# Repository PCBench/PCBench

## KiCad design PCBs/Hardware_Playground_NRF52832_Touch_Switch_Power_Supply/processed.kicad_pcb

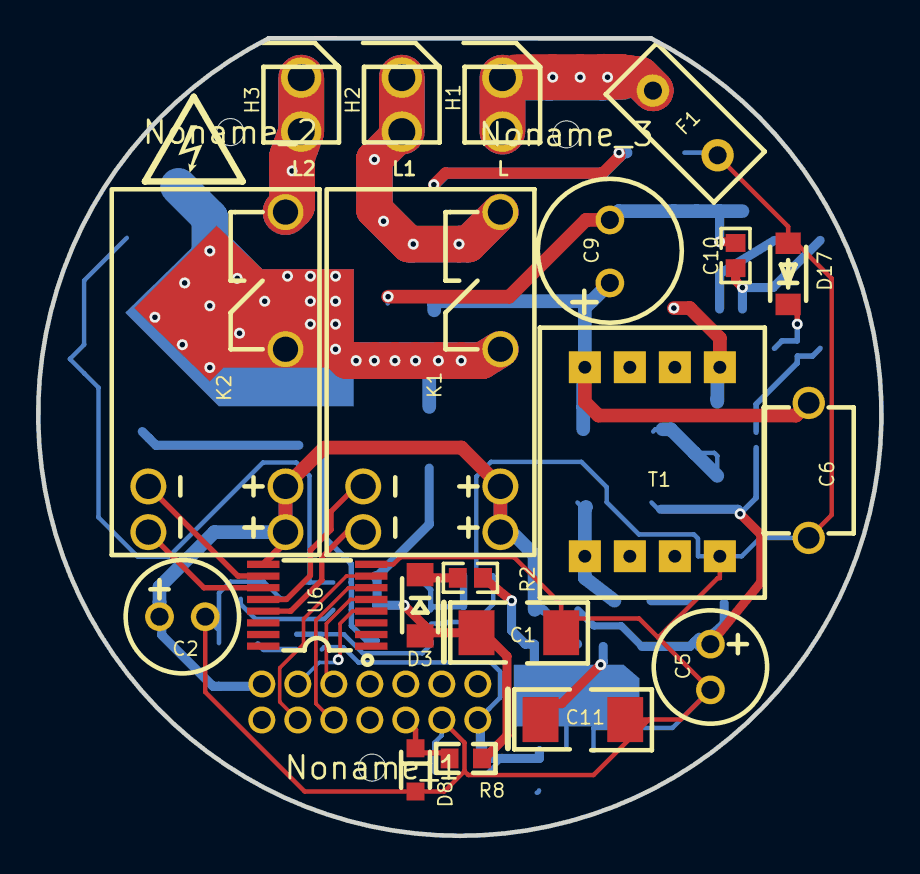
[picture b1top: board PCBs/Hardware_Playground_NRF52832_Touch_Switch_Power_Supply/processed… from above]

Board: 2 copper layers, 46.8 x 44.3 mm, 56 parts (0 on the bottom side), 37 nets.

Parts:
C1, C11: 22uF; CAP-SMD_L6.0-W3.2
C2, C5: 330uF; CAP-TH_BD6.3-P2.50-D1.0-FD
C3: CAP-SMD_L3.5-W2.8-R-RD
C4: 680nF; 0805
C6: 1nF; CAP-TH_L7.0-W5.0-P7.50-D1.2
C7: 27pF; 0805
C9: 4.7uF; CAP-TH_BD8.0-P3.50-D1.0-FD
C10: 100nF; 0603
CN1: 2X7P; A2005WV-2X7P
D1: B340LB-13-F; SMB_L4.6-W3.6-LS5.3-RD
D2, D3: 1N4007W; SOD-123FL_L2.7-W1.8-LS3.8-RD
D4, D7, D12: BAV21WS; SOD-323_L1.8-W1.3-LS2.5-RD
D5, D6: MMSZ5242BS; SOD-323_L1.8-W1.3-LS2.5-RD
D8: BZT52C3V3S; SOD-323_L1.8-W1.3-LS2.5-RD
D13: MB6S; MBS
D14: SS14; SMA_L4.3-W2.6-LS5.2-FD
D15: SMBJ130A; SMB_L4.6-W3.6-LS5.3-RD
D16: US1M; SMA(DO-214AC)
D17: MMSZ5242; SOD-123_L2.8-W1.8-LS3.7-RD
F1: SMT1500A; FUSE-TH_L8.5-W4.0-P5.08-D0.6
H1: L; 360273
H2: L1; 360273
H3: L2; 360273
HV2: IEC_HighVoltage; IEC_HIGHVOLTAGE_SMALL
K1, K2: HFE60-12-1HT-L2; RELAY-TH_HFE60-12-1HST-L2
LG: my_logo; gge1185
Noname_1, Noname_2, Noname_3: MountingHole_1.50mm
Q1: IRLR8726PBF; TO-252-2_L6.6-W6.1-P4.57-LS9.9-BR-CW
Q2: MMBT3904; SOT-23(SOT-23-3)
R1, R2: 47; 0603
R3: 20K; 0402
R4: 10K; 0402
R5, R6: 100K; R0402
R7: 33K; 0402
R8: 1K; R0603
R16: 390; 0805
R18: 22; 0402
R19: 1K; 0402
R20: 10; 1206
T1: EE10A-1
U1: LM321; SOT-23-5_L3.0-W1.7-P0.95-LS2.8-BL
U2: MCP1703T-3302; SOT-89-3_L4.5-W2.5-P1.50-LS4.2-BR
U3: EL357; SOP-4_P2.54
U4: LNK364DN-TL; SO-8_7P-L4.9-W3.9-P1.27-LS5.9-BL-PE3
U6: TPL7407LPWR; TSSOP-16_L5.0-W4.4-P0.65-LS6.4-BL

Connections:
+3V3: C3.1, CN1.2, R4.2, U2.3
+12V: C2.1, CN1.13, D4.1, D5.1, D7.1, K1.1, K1.2, K2.1, K2.2, U6.9
AC_DC_N: D13.1, H2.1, H2.2, K1.8
C9_1: C6.2, C9.1, D13.3, D15.2, T1.1
CH1_RST: CN1.9, U6.5
CH1_SET: CN1.11, U6.4
CH2_RST: CN1.12, U6.7
CH2_SET: CN1.10, U6.6
D1_1: D1.1, D2.2, K1.5, K2.5, Q1.2
D12_2: C5.1, C7.2, D7.2, D12.2, D14.2, R18.2
D13_2: D13.2, R20.2
D16_2: D15.1, D16.2
F1_2: F1.2, H1.1, H1.2
GND: C1.2, C2.2, C3.2, C4.1, C5.2, C6.1, C11.2, CN1.4, D1.2, D5.2, D8.2, D17.2, F1.1, Q1.3, Q2.2, R6.1, R7.1, R20.1, T1.5, U1.2, U2.1, U6.8
H3_1: H3.1, H3.2, K2.8
K1_15: K1.15, U6.12
K1_16: K1.16, U6.13
K2_15: K2.15, U6.10
K2_16: K2.16, U6.11
Q1_1: Q1.1, R1.2
Q2_1: Q2.1, R5.1
Q2_3: Q2.3, R3.1
R2_1: D3.1, R2.1
R2_2: C11.1, D4.2, D12.1, R2.2, U2.2
R16_2: C7.1, R16.2
T1_8: D14.1, R16.1, T1.8
U1_1: C4.2, D6.2, R7.2, U1.1
U1_3: R3.2, R4.1, U1.3
U1_4: R1.1, R5.2, R6.2, U1.4
U1_5: C1.1, D2.1, D3.2, D6.1, R8.2, U1.5
U3_1: R18.1, R19.2, U3.1
U3_2: D17.1, R19.1, U3.2
U3_3: U3.3, U4.2
U3_4: C10.1, U3.4, U4.1
U4_4: D16.1, T1.4, U4.4
U4_5: C9.2, C10.2, D13.4, U4.5, U4.6, U4.7, U4.8
VSENSE: CN1.6, D8.1, R8.1

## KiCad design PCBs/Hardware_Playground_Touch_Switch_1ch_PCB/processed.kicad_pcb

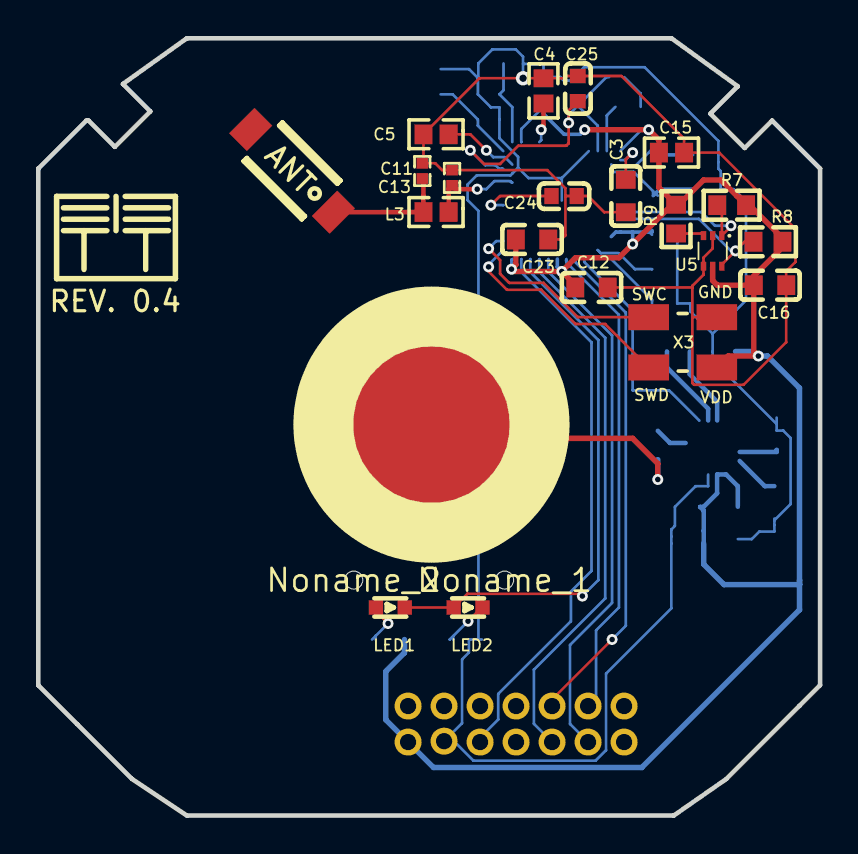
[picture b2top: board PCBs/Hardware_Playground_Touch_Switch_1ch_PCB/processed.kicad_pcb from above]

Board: 2 copper layers, 43.4 x 43.2 mm, 49 parts (0 on the bottom side), 37 nets.

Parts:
ALG: my_logo; ggeac4e8891367b2b2c
C1, C15, C17: 1uF; 0603
C2, C3, C12, C16, C18, C19, C20, C23: 100nF; C0603
C4: N.C.; 0603
C5: 100pF; 0603
C6: 2.2nF; C0603
C7, C8, C9, C10: 22pF; 0603
C11, C13: 0.5pF; 0402
C14, C21, C22: 4.7uF; 0603
C24: 820pF; C0603
C25: 47nF; C0603
CN1: 2X7P; HDR-TH_14P-P2.00-V-R2-C7-S2.00_A2005HWV-2X7P
H1: PROG; CONNECTER_SMD_1.27_1X4_D180
L2: 10uH; 0603
L3: 3.3nH; 0603
L4: 15nH; 0402
LED1: RED; LED-SMD_0603-T
LED2: BLUE; LED-SMD_0603-T
Noname_1, Noname_2: MountingHole_1.00mm
R5, R6, R7, R8, R9: 4.7K; R0603
R10: 560; R0603
U1: NRF52840-QIAA-R; AQFN-73_L7.0-W7.0-P0.50-BL-EP4.8
U3: Antenna 2.4GHz; AN6520
U5: TMP112; SOT-563_L1.6-W1.2-P0.50-LS1.6-BL
U6: CY8C4014LQI-421T; QFN-16_L3.0-W3.0-P0.50-BL-EP1.7
U7: TS1; LIVOLO_TOUCH_PAD
X1: 32MHz; OSC-SMD_4P-L2.0-W1.6-BL
X2: 32.768KHz; FC-135R_L3.2-W1.5
X3: ICSP; SWD4_5032

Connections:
ANT: C11.1, L3.1, U1.H23
C4_2: C4.2, U1.A18
CH1_LED: LED1.1, LED2.2, U1.AD20
DCC: L2.1, U1.B3
DEC4_6: C1.1, C25.2, L4.2, U1.B5, U1.E24
GND: C1.2, C2.1, C3.2, C4.1, C5.2, C6.2, C7.2, C8.2, C9.1, C10.1, C11.2, C12.1, C13.2, C14.1, C15.1, C16.2, C17.1, C18.1, C19.1, C20.1, C21.1, C22.1, C23.1, C24.1, C25.1, CN1.11, H1.3, R5.2, U1.0, U1.B7, U1.F23, U5.2, U5.4, U6.7, X1.2, X1.4, X3.3
L2_2: L2.2, L4.1
L3_2: C13.1, L3.2, U3.1
LED2_1: LED2.1, R5.1
MTO: U1.AD8, U6.13
R1_RST: CN1.6, U1.AD10
R1_SET: CN1.4, U1.AD12
R2_RST: CN1.3, U1.AD16
R2_SET: CN1.5, U1.AD18
R6_1: LED1.2, R6.1
R9_1: R9.1, U5.3
R10_1: R10.1, U7.1
SCL: R7.2, U1.N1, U5.1
SDA: R8.2, U1.R1, U5.6
SWC: H1.2, U6.15
SWCLK: U1.AA24, X3.4
SWD: H1.1, U6.14
SWDIO: U1.AC24, X3.1
U1_AC5: C21.2, U1.AC5
U1_AD2: C22.2, U1.AD2
U1_C1: C3.1, U1.C1
U1_D23: C5.1, U1.D23
U1_N24: C24.2, U1.N24
U6_3: C6.1, U6.3
U6_4: C19.2, U6.4
U6_11: R10.2, U6.11
VDD: C2.2, C12.2, C14.2, C15.2, C16.1, C17.2, C18.2, C20.2, C23.2, CN1.13, H1.4, R6.2, R7.1, R8.1, R9.2, U1.A22, U1.AD14, U1.AD23, U1.B1, U1.W1, U1.Y2, U5.5, U6.5, U6.6, X3.2
VSENSE: CN1.9, U1.AD22
XC1: C7.1, U1.B24, X1.1
XC2: C8.1, U1.A23, X1.3
XL1: C9.2, U1.D2, X2.1
XL2: C10.2, U1.F2, X2.2

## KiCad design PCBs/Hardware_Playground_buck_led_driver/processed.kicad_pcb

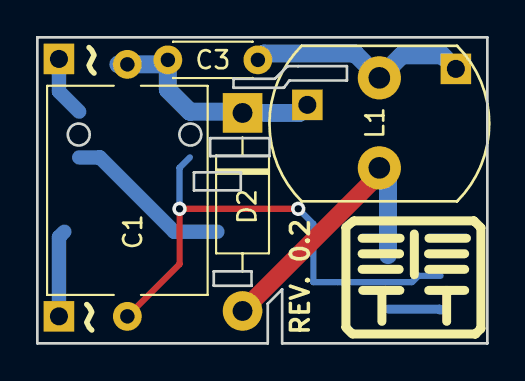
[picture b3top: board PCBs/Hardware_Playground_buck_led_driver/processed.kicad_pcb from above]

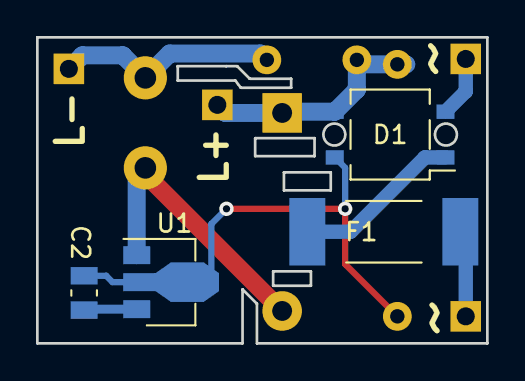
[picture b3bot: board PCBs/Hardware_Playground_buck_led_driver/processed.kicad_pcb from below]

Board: 2 copper layers, 25.0 x 17.0 mm, 12 parts (4 on the bottom side), 8 nets.

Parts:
C1: 100n/400Vdc; C_Rect_L11.5mm_W8.8mm_P10.00mm_MKT
C2: 0.1u; C_0805_2012Metric
C3: 10n/100Vdc; C_Disc_D4.3mm_W1.9mm_P5.00mm
D1: MB10S; TO-269AA
D2: MUR160; D_DO-41_SOD81_P10.16mm_Horizontal
F1: 0.5A; R_2512_6332Metric
J1, J2: AC_IN; PinHeader_1x01_P2.54mm_Vertical
J3: LED+; PinHeader_1x01_P2.54mm_Vertical
J4: LED-; PinHeader_1x01_P2.54mm_Vertical
L1: 39mH; L_Radial_D12.0mm_P5.00mm_Neosid_SD12k_style2
U1: HV9922N8-G; SOT-89-3

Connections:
GND: C1.2, C2.1, D1.4, U1.2
unnamed: C1.1, C3.1, D1.3, D2.1, J3.1
unnamed: C2.2, U1.3
unnamed: C3.2, J4.1, L1.1
unnamed: D1.1, F1.1
unnamed: D1.2, J1.1
unnamed: D2.2, L1.2, U1.1
unnamed: F1.2, J2.1

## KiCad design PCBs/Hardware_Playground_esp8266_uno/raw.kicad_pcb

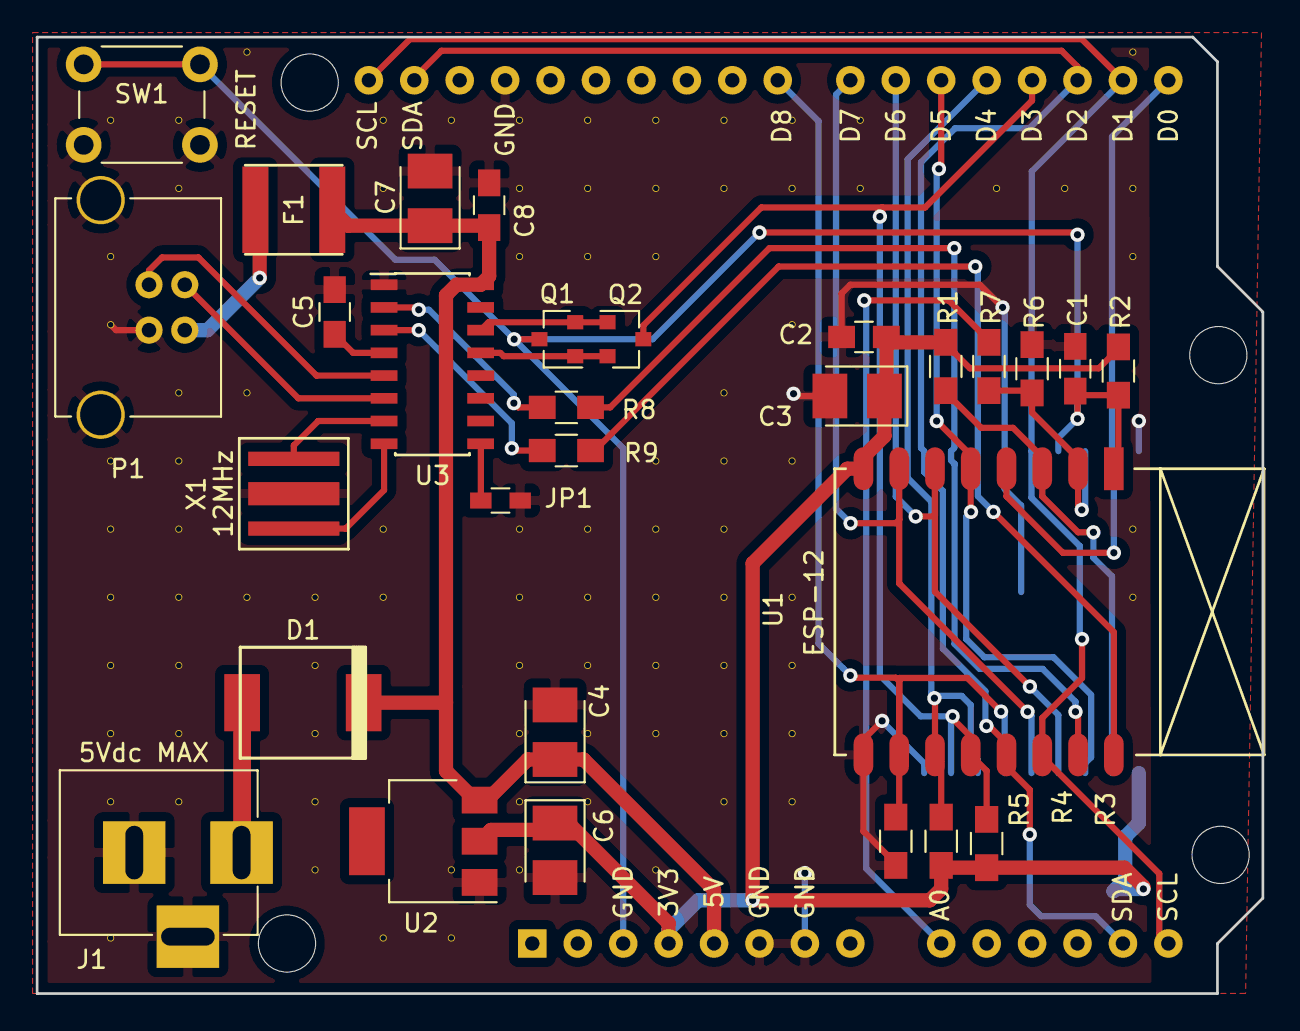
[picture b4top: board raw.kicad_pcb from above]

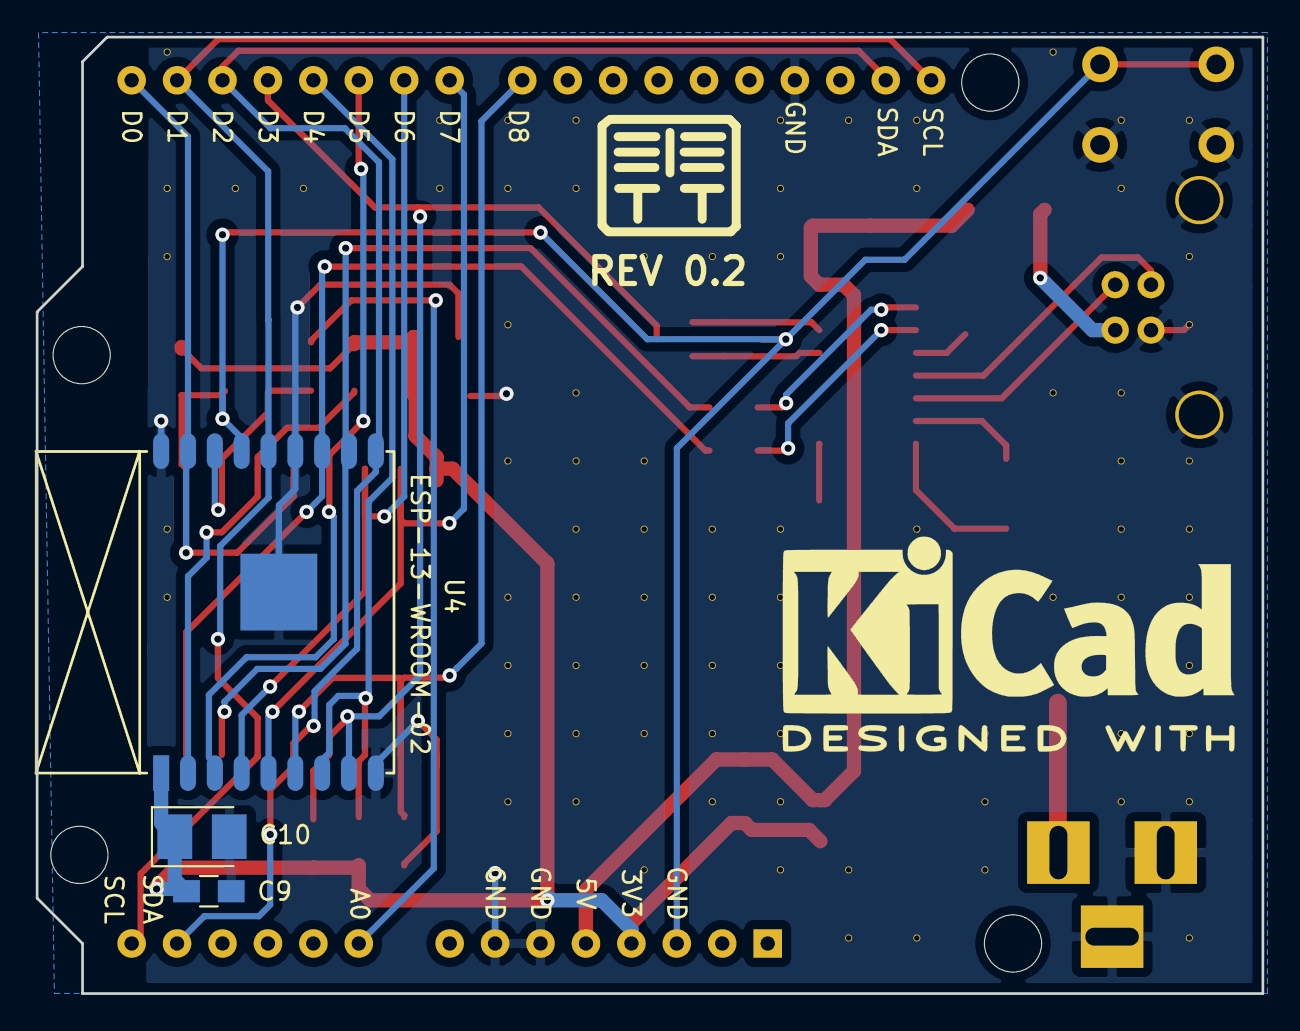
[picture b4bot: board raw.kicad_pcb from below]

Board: 2 copper layers, 68.5 x 53.5 mm, 120 parts (4 on the bottom side), 30 nets.

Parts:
A1: Arduino_UNO_R3
C1, C2, C8, C9: 100n; C_0805_HandSoldering
C3, C7, C10: 10u; CP_Tantalum_Case-B_EIA-3528-21_Reflow
C4, C6: 22u; CP_Tantalum_Case-B_EIA-3528-21_Reflow
C5: 10n; C_0805_HandSoldering
D1: SS34; do214ab
F1: MF-SMDF050; mf-smdf050
J1: Barrel_Jack; BARREL_JACK
JP1: CTS; R_0603_HandSoldering
P1: USB; USB_B
Q1, Q2: 2N2222; SOT-23
R1, R2, R3, R4, R5: 10K; R_0805_HandSoldering
R6: 100K; R_0805_HandSoldering
R7: 220K; R_0805_HandSoldering
R8, R9: 470; R_0805_HandSoldering
SW1: RESET; SW_PUSH_6mm
U1: ESP-12
U2: AMS1117-3.3; SOT-223
U3: CH340G; SOIC-16_3.9x9.9mm_Pitch1.27mm
U4: ESP-13-WROOM-02
V3_2, V3_4, V3_5, V3_7, V3_8, V3_9, V3_10, V3_11, V3_12, V3_14, V4_2, V4_3, V4_6, V4_7, V4_8, V4_9, V4_10, V4_11, V4_12, V5_1, V5_6, V5_9, V6_9, V6_10, V6_11, V6_12, V6_13, V7_2, V7_3, V7_8, V7_9, V7_14, V8_2, V8_13, V8_14, V9_2, V9_3, V9_4, V9_8, V9_9, V9_10, V9_11, V9_12, V9_13, V10_2, V10_3, V10_4, V10_8, V10_9, V10_10, V10_11, V10_12, V11_2, V11_3, V11_4, V11_7, V11_8, V11_9, V11_10, V11_11, V11_13, V12_2, V12_3, V12_6, V12_7, V12_8, V12_9, V12_10, V12_11, V12_12, V13_2, V13_3, V13_5, V13_7, V13_9, V13_10, V13_11, V13_12, V14_2, V14_3, V16_3, V17_3, V18_1, V18_3, V18_4, V18_8, V18_9: AUTO_VIA; VIA_MATRIX
X1: 12MHz; ZTTCS-3

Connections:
+3V3: A1.4, C2.2, C3.1, C6.1, C9.2, C10.1, R1.2, R2.2, R3.2, R4.2, U1.8, U2.2, U4.1
+5V: A1.5, C4.1, C7.1, C8.2, D1.1, F1.1, U2.3, U3.16
/A0: A1.9, R7.1
/ADC: R6.1, R7.2, U1.2, U4.16
/DTR: Q1.1, Q2.2, U3.13
/EN: R1.1, U1.3, U4.2
/GPIO0: A1.18, Q2.3, R3.1, U1.12, U4.8
/GPIO2: A1.19, R4.1, U1.11, U4.7
/GPIO4: A1.13, A1.17, A1.31, U1.13, U4.10
/GPIO5: A1.14, A1.16, A1.32, U1.14, U4.14
/GPIO12: A1.21, U1.6, U4.4
/GPIO13: A1.22, U1.7, U4.5
/GPIO14: A1.20, U1.5, U4.3
/GPIO15: A1.23, R5.1, U1.10, U4.6
/GPIO16: A1.15, U1.4, U4.17
/RESET: A1.3, C1.2, Q1.3, R2.1, SW1.1, U1.1, U4.15
/RTS: Q1.2, Q2.1, U3.14
/RX: R8.2, U1.15, U4.11
/TX: R9.2, U1.16, U4.12
GND: A1.6, A1.7, A1.29, C1.1, C2.1, C3.2, C4.2, C5.2, C6.2, C7.2, C8.1, C9.1, C10.2, J1.2, J1.3, JP1.1, P1.4, P1.5, R5.2, R6.2, SW1.2, U1.9, U2.1, U3.1, U4.9, U4.13, U4.18, U4.PAD, V3_2.1, V3_4.1, V3_5.1, V3_7.1, V3_8.1, V3_9.1, V3_10.1, V3_11.1, V3_12.1, V3_14.1, V4_2.1, V4_3.1, V4_6.1, V4_7.1, V4_8.1, V4_9.1, V4_10.1, V4_11.1, V4_12.1, V5_1.1, V5_6.1, V5_9.1, V6_9.1, V6_10.1, V6_11.1, V6_12.1, V6_13.1, V7_2.1, V7_3.1, V7_8.1, V7_9.1, V7_14.1, V8_2.1, V8_13.1, V8_14.1, V9_2.1, V9_3.1, V9_4.1, V9_8.1, V9_9.1, V9_10.1, V9_11.1, V9_12.1, V9_13.1, V10_2.1, V10_3.1, V10_4.1, V10_8.1, V10_9.1, V10_10.1, V10_11.1, V10_12.1, V11_2.1, V11_3.1, V11_4.1, V11_7.1, V11_8.1, V11_9.1, V11_10.1, V11_11.1, V11_13.1, V12_2.1, V12_3.1, V12_6.1, V12_7.1, V12_8.1, V12_9.1, V12_10.1, V12_11.1, V12_12.1, V13_2.1, V13_3.1, V13_5.1, V13_7.1, V13_9.1, V13_10.1, V13_11.1, V13_12.1, V14_2.1, V14_3.1, V16_3.1, V17_3.1, V18_1.1, V18_3.1, V18_4.1, V18_8.1, V18_9.1, X1.2
unnamed: C5.1, U3.4
unnamed: D1.2, J1.1
unnamed: F1.2, P1.1
unnamed: JP1.2, U3.9
unnamed: P1.2, U3.6
unnamed: P1.3, U3.5
unnamed: R8.1, U3.2
unnamed: R9.1, U3.3
unnamed: U3.7, X1.1
unnamed: U3.8, X1.3

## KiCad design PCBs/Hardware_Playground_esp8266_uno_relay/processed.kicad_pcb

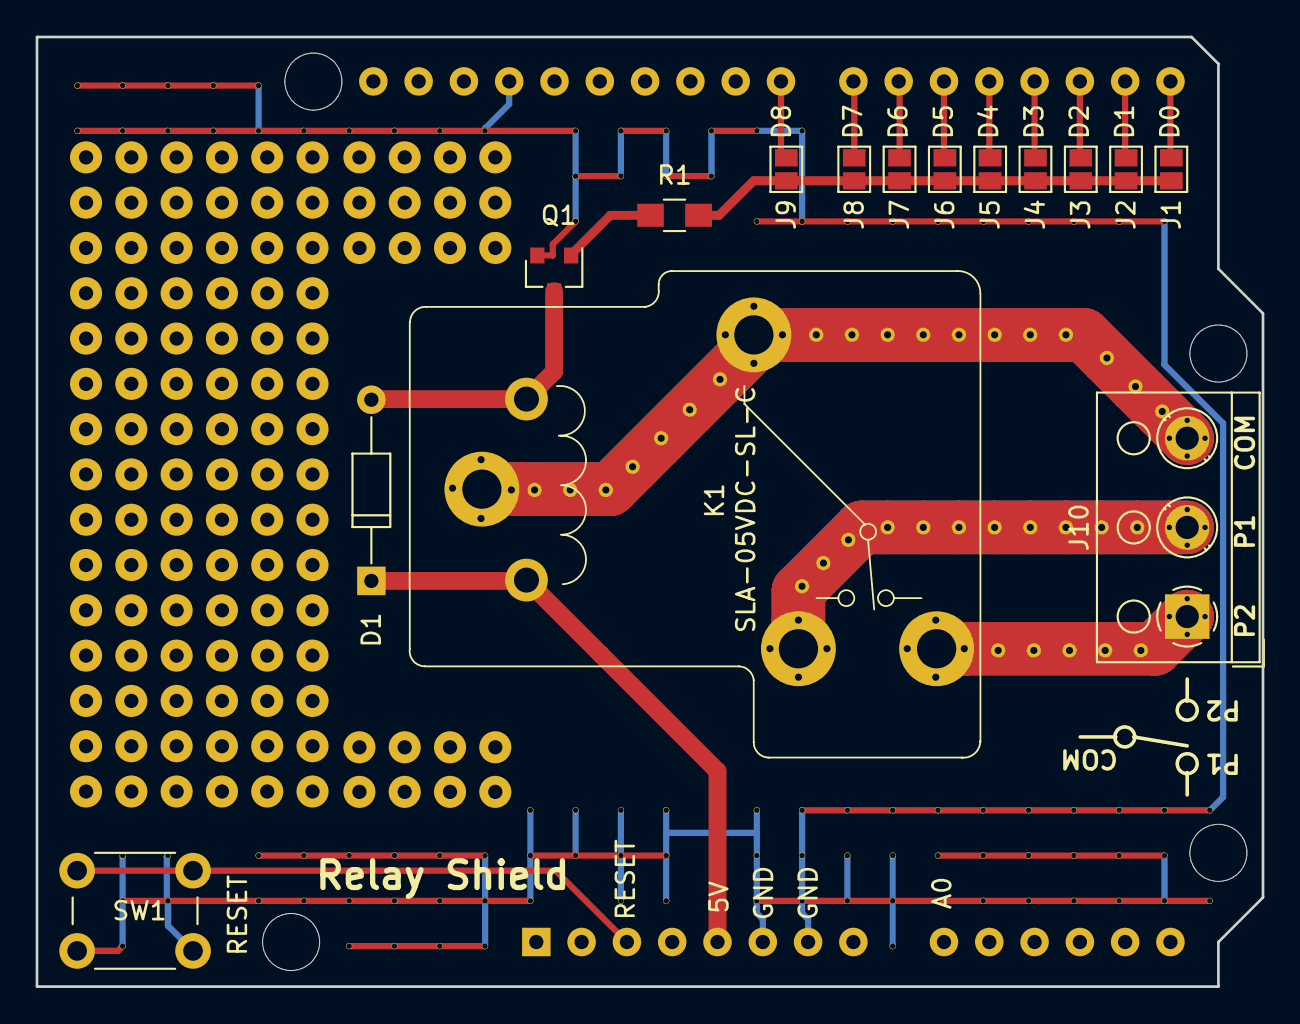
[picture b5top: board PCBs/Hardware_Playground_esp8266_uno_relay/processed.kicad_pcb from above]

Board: 2 copper layers, 68.8 x 53.2 mm, 179 parts (1 on the bottom side), 18 nets.

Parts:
A1: Arduino_UNO_R3
D1: 1N4148; D_DO-35_SOD27_P10.16mm_Horizontal
J1, J2, J3, J4, J5, J6, J7, J8, J9: GS2
J10: R_CON; TerminalBlock_RND_205-00002_Pitch5.00mm
K1: SLA-05VDC-SL-C; SLA-5VDC-SL
Q1: MMBT2222; SOT-23
R1: 1K; R_0805_HandSoldering
SW1: RESET; SW_PUSH_6mm
V5_2, V5_3, V6_2, V6_3, V6_19, V6_20, V6_21, V7_2, V7_3, V7_19, V7_20, V8_2, V8_3, V9_2, V9_3, V9_19, V9_20, V10_3, V10_19, V10_20, V11_3, V11_19, V11_20, V11_21, V12_3, V12_19, V12_20, V12_21, V13_3, V13_19, V13_20, V13_21, V14_3, V14_19, V14_20, V14_21, V15_18, V15_19, V15_20, V16_3, V16_4, V16_5, V16_18, V16_19, V17_3, V17_4, V17_18, V17_19, V17_20, V18_3, V18_4, V18_18, V18_19, V18_20, V19_3, V19_4, V20_3, V20_5, V20_18, V20_19, V20_20, V21_3, V21_5, V21_18, V21_18_2, V21_18_3, V21_18_4, V21_18_5, V21_18_6, V21_18_7, V21_18_8, V21_18_9, V21_18_10, V21_18_11, V21_18_12, V21_18_13, V21_18_14, V21_18_15, V21_18_16, V21_18_17, V21_18_18, V21_18_19, V21_18_20, V21_18_21, V21_18_22, V21_18_23, V21_18_24, V21_18_25, V21_18_26, V21_18_27, V21_18_28, V21_18_29, V21_18_30, V21_18_31, V21_18_32, V21_18_33, V21_18_34, V21_18_35, V21_18_36, V21_18_37, V21_18_38, V21_18_39, V21_18_40, V21_18_41, V21_18_42, V21_18_43, V21_18_44, V21_18_45, V21_18_46, V21_18_47, V21_18_48, V21_18_49, V21_18_50, V21_18_51, V21_18_52, V21_18_53, V21_18_54, V21_18_55, V21_18_56, V21_18_57, V21_18_58, V21_18_59, V21_18_60, V21_18_61, V21_18_62, V21_18_63, V21_19, V21_20, V22_5, V22_18, V22_19, V22_20, V23_5, V23_18, V23_19, V23_20, V23_21, V24_5, V24_18, V24_19, V24_20, V25_5, V25_18, V25_19, V25_20, V26_5, V26_18, V26_19, V26_20, V27_5, V27_18, V27_19, V27_20, V28_5, V28_18, V28_19, V28_20, V29_5, V29_18, V29_19, V29_20, V30_18, V30_20: AUTO_VIA; VIA_MATRIX

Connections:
+5V: A1.5, D1.1, K1.5
/D0: A1.15, J1.2
/D1: A1.16, J2.2
/D2: A1.17, J3.2
/D3: A1.18, J4.2
/D4: A1.19, J5.2
/D5: A1.20, J6.2
/D6: A1.21, J7.2
/D7: A1.22, J8.2
/D8: A1.23, J9.2
/REL1: J10.3, K1.1, V21_18_26.1, V21_18_27.1, V21_18_28.1, V21_18_29.1, V21_18_30.1, V21_18_31.1, V21_18_32.1, V21_18_33.1, V21_18_34.1, V21_18_35.1, V21_18_36.1, V21_18_37.1, V21_18_38.1, V21_18_39.1, V21_18_40.1, V21_18_41.1, V21_18_42.1, V21_18_43.1, V21_18_44.1, V21_18_45.1, V21_18_46.1, V21_18_47.1, V21_18_48.1, V21_18_49.1, V21_18_50.1, V21_18_51.1, V21_18_60.1, V21_18_61.1, V21_18_62.1, V21_18_63.1
/REL3: J10.1, K1.3, V21_18_13.1, V21_18_14.1, V21_18_15.1, V21_18_16.1, V21_18_17.1, V21_18_18.1, V21_18_19.1, V21_18_20.1, V21_18_21.1, V21_18_52.1, V21_18_53.1, V21_18_54.1, V21_18_55.1
/REL4: J10.2, K1.4, V21_18_2.1, V21_18_3.1, V21_18_4.1, V21_18_5.1, V21_18_6.1, V21_18_7.1, V21_18_8.1, V21_18_9.1, V21_18_10.1, V21_18_11.1, V21_18_12.1, V21_18_22.1, V21_18_23.1, V21_18_24.1, V21_18_25.1, V21_18_56.1, V21_18_57.1, V21_18_58.1, V21_18_59.1
/RELAY_CMD: J1.1, J2.1, J3.1, J4.1, J5.1, J6.1, J7.1, J8.1, J9.1, R1.2
GND: A1.6, A1.7, A1.29, Q1.2, SW1.2, V5_2.1, V5_3.1, V6_2.1, V6_3.1, V6_19.1, V6_20.1, V6_21.1, V7_2.1, V7_3.1, V7_19.1, V7_20.1, V8_2.1, V8_3.1, V9_2.1, V9_3.1, V9_19.1, V9_20.1, V10_3.1, V10_19.1, V10_20.1, V11_3.1, V11_19.1, V11_20.1, V11_21.1, V12_3.1, V12_19.1, V12_20.1, V12_21.1, V13_3.1, V13_19.1, V13_20.1, V13_21.1, V14_3.1, V14_19.1, V14_20.1, V14_21.1, V15_18.1, V15_19.1, V15_20.1, V16_3.1, V16_4.1, V16_5.1, V16_18.1, V16_19.1, V17_3.1, V17_4.1, V17_18.1, V17_19.1, V17_20.1, V18_3.1, V18_4.1, V18_18.1, V18_19.1, V18_20.1, V19_3.1, V19_4.1, V20_3.1, V20_5.1, V20_18.1, V20_19.1, V20_20.1, V21_3.1, V21_5.1, V21_18.1, V21_19.1, V21_20.1, V22_5.1, V22_18.1, V22_19.1, V22_20.1, V23_5.1, V23_18.1, V23_19.1, V23_20.1, V23_21.1, V24_5.1, V24_18.1, V24_19.1, V24_20.1, V25_5.1, V25_18.1, V25_19.1, V25_20.1, V26_5.1, V26_18.1, V26_19.1, V26_20.1, V27_5.1, V27_18.1, V27_19.1, V27_20.1, V28_5.1, V28_18.1, V28_19.1, V28_20.1, V29_5.1, V29_18.1, V29_19.1, V29_20.1, V30_18.1, V30_20.1
unnamed: A1.3, SW1.1
unnamed: D1.2, K1.2, Q1.3
unnamed: Q1.1, R1.1

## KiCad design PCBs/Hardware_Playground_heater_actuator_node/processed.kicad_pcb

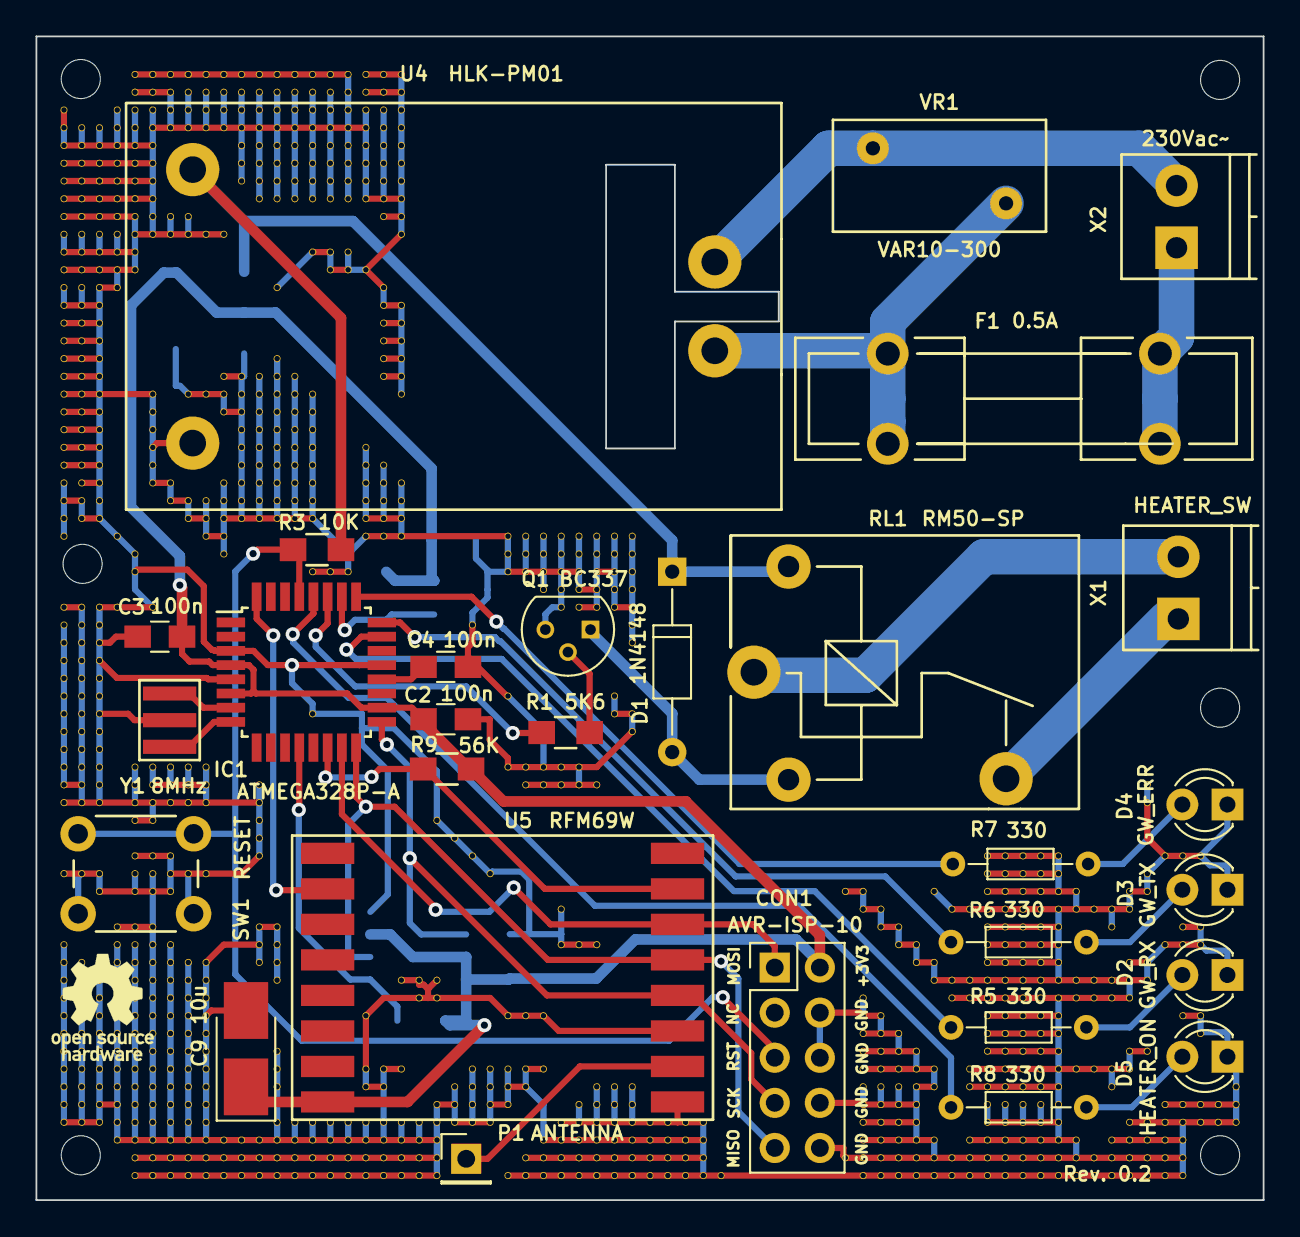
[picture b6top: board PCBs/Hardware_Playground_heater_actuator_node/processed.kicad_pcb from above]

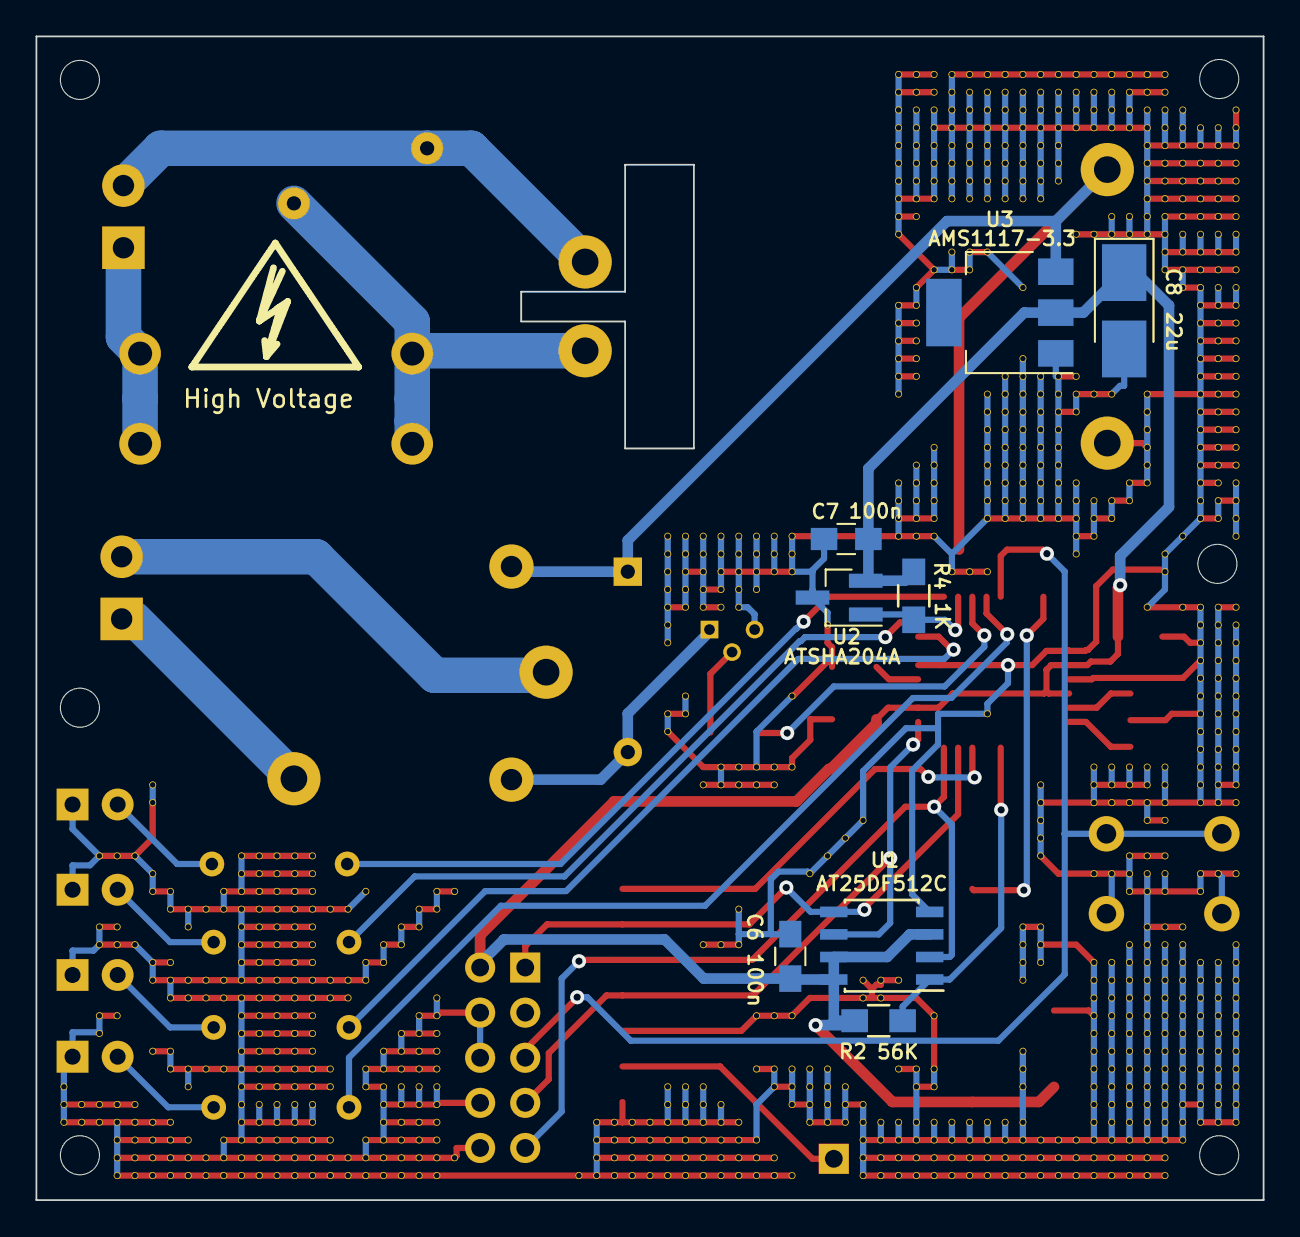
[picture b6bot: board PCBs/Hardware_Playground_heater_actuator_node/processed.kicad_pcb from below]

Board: 2 copper layers, 69.1 x 65.5 mm, 982 parts (8 on the bottom side), 31 nets.

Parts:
C2, C3, C4, C6, C7: 100n; C_0805_HandSoldering
C8: 22u; CP_Tantalum_Case-B_EIA-3528-21_Hand
C9: 10u; CP_Tantalum_Case-B_EIA-3528-21_Hand
CON1: AVR-ISP-10; Pin_Header_Straight_2x05_Pitch2.54mm
D1: 1N4148; D_DO-35_SOD27_P10.16mm_Horizontal
D2: GW_RX; LED_D3.0mm
D3: GW_TX; LED_D3.0mm
D4: GW_ERR; LED_D3.0mm
D5: HEATER_ON; LED_D3.0mm
F1: 0.5A; Fuseholder5x20_horiz_open_lateral_Type-II
IC1: ATMEGA328P-A; TQFP-32_7x7mm_Pitch0.8mm
P1: ANTENNA; Pin_Header_Straight_1x01_Pitch2.54mm
Q1: BC337; TO-92_Molded_Narrow
R1: 5K6; R_0805_HandSoldering
R2, R9: 56K; R_0805_HandSoldering
R3: 10K; R_0805_HandSoldering
R4: 1K; R_0805_HandSoldering
R5, R6, R7, R8: 330; R_Axial_DIN0204_L3.6mm_D1.6mm_P7.62mm_Horizontal
RL1: RM50-SP; RM50_SP
SW1: RESET; SW_PUSH_6mm
U1: AT25DF512C; SOIC-8_3.9x4.9mm_Pitch1.27mm
U2: ATSHA204A; SOT-23_Handsoldering
U3: AMS1117-3.3; SOT-223
U4: HLK-PM01
U5: RFM69W; RFM69HW_SMD_Handsoldering
V10_6, V10_7, V10_8, V10_9, V10_10, V10_11, V10_12, V10_13, V10_14, V10_15, V10_16, V10_17, V10_18, V10_19, V10_20, V10_21, V10_22, V10_23, V10_24, V10_25, V10_26, V10_27, V10_28, V10_29, V10_30, V10_34, V10_35, V10_36, V10_37, V10_38, V10_39, V10_40, V10_41, V10_42, V10_43, V10_44, V10_45, V10_49, V10_53, V10_54, V10_55, V10_56, V10_57, V10_58, V10_59, V10_60, V10_61, V10_62, V10_63, V11_7, V11_8, V11_9, V11_10, V11_11, V11_12, V11_13, V11_14, V11_15, V11_16, V11_17, V11_18, V11_19, V11_20, V11_21, V11_22, V11_23, V11_24, V11_25, V11_26, V11_27, V11_28, V11_29, V11_34, V11_35, V11_36, V11_37, V11_38, V11_39, V11_40, V11_41, V11_42, V11_43, V11_44, V11_45, V11_49, V11_54, V11_55, V11_56, V11_57, V11_58, V11_59, V11_60, V11_61, V11_62, V11_63, V12_7, V12_8, V12_9, V12_10, V12_11, V12_12, V12_13, V12_14, V12_15, V12_16, V12_17, V12_18, V12_19, V12_20, V12_21, V12_22, V12_23, V12_24, V12_25, V12_26, V12_27, V12_28, V12_29, V12_34, V12_35, V12_36, V12_37, V12_38, V12_39, V12_40, V12_41, V12_42, V12_43, V12_44, V12_45, V12_49, V12_50, V12_54, V12_55, V12_56, V12_57, V12_58, V12_59, V12_60, V12_61, V12_62, V12_63, V13_6, V13_7, V13_8, V13_9, V13_10, V13_11, V13_12, V13_13, V13_14, V13_15, V13_16, V13_30, V13_34, V13_52, V13_53, V13_54, V13_55, V13_56, V13_57, V13_58, V13_59, V13_60, V13_61, V13_62, V13_63, V13_64, V14_4, V14_5, V14_6, V14_7, V14_8, V14_9, V14_10, V14_11, V14_12, V14_13, V14_14, V14_15, V14_31, V14_32, V14_43, V14_44, V14_45, V14_46, V14_48, V14_49, V14_50, V14_52, V14_53, V14_54, V14_55, V14_56, V14_57, V14_58, V14_59, V14_60, V14_61, V14_62, V14_63, V14_64, V14_65, V14_66, V15_4, V15_5, V15_6, V15_7, V15_8, V15_9, V15_10, V15_11, V15_12, V15_13, V15_22, V15_23, V15_24, V15_25, V15_26, V15_27, V15_34, V15_43, V15_44, V15_45, V15_46, V15_48, V15_49, V15_50, V15_52, V15_53, V15_54, V15_55, V15_56, V15_57, V15_58, V15_59, V15_60, V15_61, V15_62, V15_63, V15_64, V15_65, V15_66, V16_4, V16_5, V16_6, V16_7, V16_12, V16_13, V16_27, V16_28, V16_43, V16_44, V16_45, V16_48, V16_49, V16_50, V16_53, V16_54, V16_55, V16_56, V16_57, V16_58, V16_59, V16_60, V16_61, V16_62, V16_63, V16_64, V16_65, V16_66, V17_4, V17_5, V17_6, V17_7, V17_12, V17_13, V17_22, V17_28, V17_29, V17_43, V17_44, V17_45, V17_49, V17_54, V17_55, V17_56, V17_57, V17_58, V17_59, V17_60, V17_61, V17_62, V17_63, V17_64, V17_65, V17_66, V18_4, V18_5, V18_6, V18_7, V18_13, V18_22, V18_28, V18_29, V18_30, V18_43, V18_44, V18_45, V18_49, V18_54, V18_55, V18_56, V18_57, V18_58, V18_59, V18_60, V18_61, V18_62, V18_63, V18_64, V18_65, V18_66, V19_4, V19_5, V19_6, V19_7, V19_13, V19_21, V19_22, V19_23, V19_27, V19_28, V19_29, V19_30, V19_31, V19_64, V19_65, V19_66, V20_4, V20_5, V20_6, V20_7, V20_8, V20_9, V20_10, V20_21, V20_22, V20_23, V20_24, V20_25, V20_26, V20_27, V20_28, V20_29, V20_64, V20_65, V20_66, V21_4, V21_5, V21_6, V21_7, V21_8, V21_9, V21_10, V21_11, V21_21, V21_22, V21_23, V21_24, V21_25, V21_26, V21_27, V21_28, V21_29, V21_44, V21_45, V21_46, V21_47, V21_48, V21_52, V21_53, V21_54, V21_64, V21_65, V21_66, V22_4, V22_5, V22_6, V22_7, V22_8, V22_9, V22_10, V22_11, V22_16, V22_20, V22_21, V22_22, V22_23, V22_24, V22_25, V22_26, V22_27, V22_28, V22_29, V22_52, V22_53, V22_54, V22_55, V22_59, V22_60, V22_61, V22_63, V22_64, V22_65, V22_66, V23_4, V23_5, V23_6, V23_7, V23_8, V23_9, V23_10, V23_11, V23_21, V23_22, V23_23, V23_24, V23_25, V23_26, V23_27, V23_28, V23_29, V23_63, V23_64, V23_65, V23_66, V24_4, V24_5, V24_6, V24_7, V24_8, V24_9, V24_10, V24_11, V24_14, V24_22, V24_23, V24_24, V24_25, V24_26, V24_27, V24_28, V24_29, V24_32, V24_40, V24_63, V24_64, V24_65, V24_66, V25_4, V25_5, V25_6, V25_7, V25_8, V25_9, V25_10, V25_11, V25_14, V25_15, V25_32, V25_63, V25_64, V25_65, V25_66, V26_4, V26_5, V26_6, V26_7, V26_8, V26_9, V26_10, V26_11, V26_14, V26_15, V26_32, V26_63, V26_64, V26_65, V26_66, V27_4, V27_5, V27_6, V27_7, V27_8, V27_9, V27_10, V27_11, V27_15, V27_25, V27_26, V27_27, V27_28, V27_29, V27_30, V27_57, V27_60, V27_61, V27_63, V27_64, V27_65, V27_66, V28_4, V28_5, V28_6, V28_7, V28_8, V28_9, V28_10, V28_11, V28_12, V28_16, V28_17, V28_18, V28_19, V28_20, V28_21, V28_26, V28_27, V28_28, V28_29, V28_30, V28_60, V28_61, V28_63, V28_64, V28_65, V28_66, V29_4, V29_5, V29_6, V29_7, V29_8, V29_9, V29_10, V29_11, V29_12, V29_13, V29_17, V29_18, V29_19, V29_20, V29_21, V29_22, V29_27, V29_28, V29_29, V29_30, V29_55, V29_60, V29_63, V29_64, V29_65, V29_66, V30_55, V30_56, V30_63, V30_64, V30_65, V30_66, V31_46, V31_55, V31_56, V31_62, V31_63, V31_64, V31_65, V31_66, V32_47, V32_61, V32_62, V32_63, V33_35, V33_48, V33_60, V33_61, V33_62, V33_63, V34_49, V34_60, V34_61, V34_62, V34_63, V35_30, V35_31, V35_32, V35_39, V35_43, V35_57, V35_60, V35_61, V35_62, V35_66, V36_30, V36_31, V36_32, V36_43, V36_44, V36_57, V36_60, V36_61, V36_65, V36_66, V37_30, V37_31, V37_32, V37_33, V37_43, V37_44, V37_57, V37_60, V37_64, V37_65, V37_66, V38_30, V38_31, V38_32, V38_33, V38_34, V38_43, V38_44, V38_51, V38_53, V38_63, V38_64, V38_65, V38_66, V39_30, V39_31, V39_32, V39_33, V39_34, V39_43, V39_44, V39_53, V39_62, V39_63, V39_64, V39_65, V39_66, V40_30, V40_31, V40_32, V40_33, V40_34, V40_44, V40_53, V40_61, V40_62, V40_63, V40_64, V40_65, V40_66, V41_30, V41_31, V41_32, V41_33, V41_34, V41_39, V41_40, V41_61, V41_62, V41_63, V41_64, V41_65, V41_66, V42_30, V42_31, V42_32, V42_33, V42_34, V42_35, V42_36, V42_40, V42_41, V42_61, V42_62, V42_63, V42_64, V42_65, V42_66, V43_63, V43_64, V43_65, V43_66, V44_63, V44_64, V44_65, V44_66, V45_63, V45_64, V45_65, V45_66, V46_63, V46_64, V46_65, V46_66, V47_66, V54_50, V54_65, V55_50, V55_51, V55_56, V55_57, V55_58, V55_59, V55_60, V55_61, V55_62, V55_63, V55_64, V55_65, V55_66, V56_51, V56_52, V56_57, V56_58, V56_59, V56_60, V56_61, V56_62, V56_63, V56_64, V56_65, V56_66, V57_52, V57_53, V57_58, V57_59, V57_60, V57_61, V57_62, V57_63, V57_64, V57_65, V57_66, V58_53, V58_54, V58_59, V58_60, V58_61, V58_62, V58_63, V58_64, V58_65, V58_66, V59_50, V59_54, V59_55, V59_60, V59_61, V59_64, V59_65, V59_66, V60_51, V60_55, V60_56, V60_65, V60_66, V61_51, V61_55, V61_56, V61_60, V61_61, V61_64, V61_65, V61_66, V62_48, V62_49, V62_50, V62_51, V62_52, V62_53, V62_54, V62_55, V62_56, V62_57, V62_58, V62_59, V62_60, V62_61, V62_62, V62_63, V62_64, V62_65, V62_66, V63_48, V63_49, V63_50, V63_51, V63_52, V63_53, V63_54, V63_55, V63_56, V63_57, V63_58, V63_59, V63_60, V63_61, V63_62, V63_63, V63_64, V63_65, V63_66, V64_48, V64_49, V64_50, V64_51, V64_52, V64_53, V64_54, V64_55, V64_56, V64_57, V64_58, V64_59, V64_60, V64_61, V64_62, V64_63, V64_64, V64_65, V64_66, V65_48, V65_49, V65_50, V65_51, V65_52, V65_53, V65_54, V65_55, V65_56, V65_57, V65_58, V65_59, V65_60, V65_61, V65_62, V65_63, V65_64, V65_65, V65_66, V66_48, V66_49, V66_50, V66_51, V66_52, V66_53, V66_54, V66_55, V66_56, V66_57, V66_58, V66_59, V66_60, V66_61, V66_62, V66_63, V66_64, V66_65, V66_66, V67_50, V67_51, V67_55, V67_56, V67_60, V67_64, V67_65, V67_66, V68_51, V68_55, V68_56, V68_60, V68_65, V68_66, V69_51, V69_52, V69_55, V69_56, V69_60, V69_61, V69_64, V69_65, V69_66, V70_50, V70_51, V70_54, V70_55, V70_56, V70_59, V70_60, V70_63, V70_64, V70_65, V70_66, V71_44, V71_45, V71_49, V71_50, V71_54, V71_55, V71_59, V71_63, V71_64, V71_65, V71_66, V72_48, V72_53, V72_62, V72_63, V72_64, V72_65, V72_66, V73_48, V73_52, V73_53, V73_57, V73_62, V73_63, V73_64, V73_65, V73_66, V74_48, V74_52, V74_53, V74_57, V74_58, V74_62, V74_63, V75_62, V75_63, V76_61, V76_62, V76_63: AUTO_VIA; VIA_MATRIX
VR1: VAR10-300; RV_Disc_D12_W6.3_P7.5
X1: HEATER_SW; TerminalBlock_Pheonix_PT-3.5mm_2pol
X2: 230Vac~~; TerminalBlock_Pheonix_PT-3.5mm_2pol
Y1: 8MHz; ZTTCR-3

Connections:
+3V3: C2.2, C3.2, C6.1, C7.1, C8.1, C9.1, CON1.2, IC1.4, IC1.6, IC1.18, R2.2, R4.2, R9.2, U1.3, U1.7, U1.8, U2.2, U3.2, U5.8
+5V: D1.1, R3.1, RL1.A1, U3.3, U4.3
/ATSHA204A: IC1.26, R4.1, U2.1
/ERR_LED: IC1.25, R7.2
/HEATER_ON_LED: IC1.28, R8.2
/H_RELAY_CMD: IC1.27, R1.2
/MISO: CON1.9, IC1.16, U1.2, U5.13
/MOSI: CON1.1, IC1.15, U1.5, U5.14
/RFM69W_INT: IC1.32, U5.2
/RFM69W_SS: IC1.14, R9.1, U5.15
/RST: CON1.5, IC1.29, R3.2, SW1.1
/RX_LED: IC1.23, R5.2
/SCK: CON1.7, IC1.17, U1.6, U5.12
/SPI_FLASH_SS: IC1.12, R2.1, U1.1
/TX_LED: IC1.24, R6.2
GND: C2.1, C3.1, C4.1, C6.2, C7.2, C8.2, C9.2, CON1.4, CON1.6, CON1.8, CON1.10, D2.1, D3.1, D4.1, D5.1, IC1.3, IC1.5, IC1.21, Q1.3, SW1.2, U1.4, U2.3, U3.1, U4.4, U5.9, U5.11, V10_6.1, V10_7.1, V10_8.1, V10_9.1, V10_10.1, V10_11.1, V10_12.1, V10_13.1, V10_14.1, V10_15.1, V10_16.1, V10_17.1, V10_18.1, V10_19.1, V10_20.1, V10_21.1, V10_22.1, V10_23.1, V10_24.1, V10_25.1, V10_26.1, V10_27.1, V10_28.1, V10_29.1, V10_30.1, V10_34.1, V10_35.1, V10_36.1, V10_37.1, V10_38.1, V10_39.1, V10_40.1, V10_41.1, V10_42.1, V10_43.1, V10_44.1, V10_45.1, V10_49.1, V10_53.1, V10_54.1, V10_55.1, V10_56.1, V10_57.1, V10_58.1, V10_59.1, V10_60.1, V10_61.1, V10_62.1, V10_63.1, V11_7.1, V11_8.1, V11_9.1, V11_10.1, V11_11.1, V11_12.1, V11_13.1, V11_14.1, V11_15.1, V11_16.1, V11_17.1, V11_18.1, V11_19.1, V11_20.1, V11_21.1, V11_22.1, V11_23.1, V11_24.1, V11_25.1, V11_26.1, V11_27.1, V11_28.1, V11_29.1, V11_34.1, V11_35.1, V11_36.1, V11_37.1, V11_38.1, V11_39.1, V11_40.1, V11_41.1, V11_42.1, V11_43.1, V11_44.1, V11_45.1, V11_49.1, V11_54.1, V11_55.1, V11_56.1, V11_57.1, V11_58.1, V11_59.1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
unnamed: C4.2, IC1.20
unnamed: D1.2, Q1.1, RL1.A2
unnamed: D2.2, R5.1
unnamed: D3.2, R6.1
unnamed: D4.2, R7.1
unnamed: D5.2, R8.1
unnamed: F1.1, U4.1, VR1.1
unnamed: F1.2, X2.1
unnamed: IC1.7, Y1.3
unnamed: IC1.8, Y1.1
unnamed: P1.1, U5.10
unnamed: Q1.2, R1.1
unnamed: RL1.11, X1.2
unnamed: RL1.14, X1.1
unnamed: U4.2, VR1.2, X2.2
